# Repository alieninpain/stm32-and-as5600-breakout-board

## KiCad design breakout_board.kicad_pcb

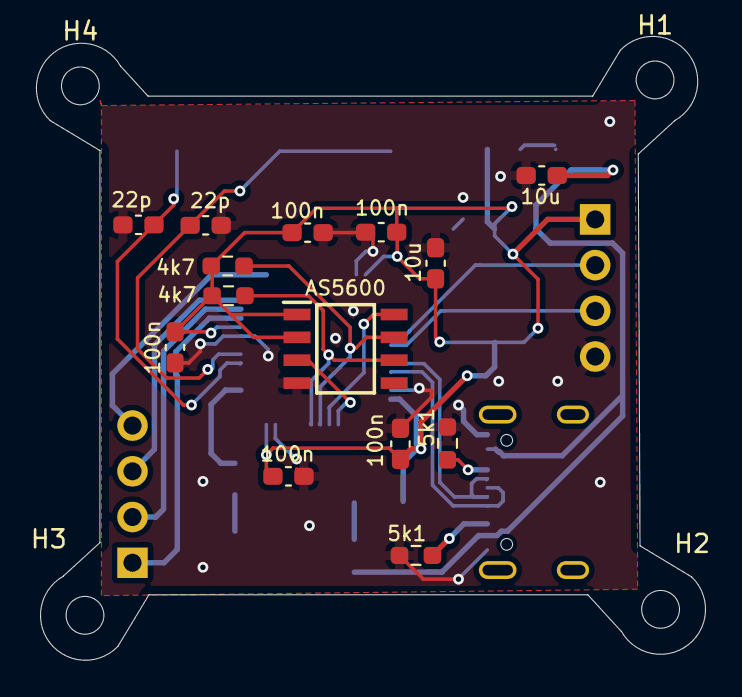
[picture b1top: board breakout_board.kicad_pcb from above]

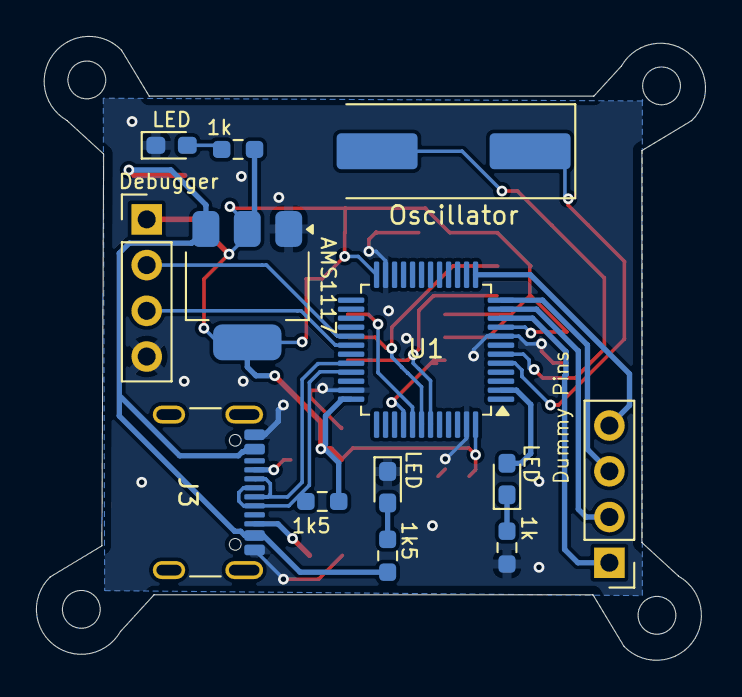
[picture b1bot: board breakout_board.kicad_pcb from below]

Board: 2 copper layers, 37.2 x 34.7 mm, 31 parts (13 on the bottom side), 23 nets.

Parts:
1k, 1k#2: 1k; R_0603_1608Metric_Pad0.98x0.95mm_HandSolder
1k5: 1k5; R_0603_1608Metric_Pad0.98x0.95mm_HandSolder
4k7: 4.7k; R_0603_1608Metric_Pad0.98x0.95mm_HandSolder
5k1: 5k1; R_0603_1608Metric_Pad0.98x0.95mm_HandSolder
10u: 10u; C_0603_1608Metric_Pad1.08x0.95mm_HandSolder
22p: 22p; C_0603_1608Metric_Pad1.08x0.95mm_HandSolder
100n: 100n; C_0603_1608Metric_Pad1.08x0.95mm_HandSolder
AMS1117: AMS1117-3.3; SOT-223-3_TabPin2
AS5600: AS5600-ASOT; SOIC127P600X175-8N
C6: 100n; C_0603_1608Metric_Pad1.08x0.95mm_HandSolder
C7: 22p; C_0603_1608Metric_Pad1.08x0.95mm_HandSolder
C9: 10u; C_0603_1608Metric_Pad1.08x0.95mm_HandSolder
D1, D2: LED; LED_0603_1608Metric_Pad1.05x0.95mm_HandSolder
DC, DC4: 100n; C_0603_1608Metric_Pad1.08x0.95mm_HandSolder
DC#2: 100n; C_0603_1608Metric_Pad1.08x0.95mm_HandSolder
H1, H2, H3, H4: MountingHole; MountingHole_2.1mm
J1: Dummy Pins; PinHeader_1x04_P2.54mm_Vertical
J2: Debugger; PinHeader_1x04_P2.54mm_Vertical
J3: USB_C_Receptacle_USB2.0_16P; USB_C_Receptacle_GCT_USB4105-xx-A_16P_TopMnt_Horizontal
LED: LED; LED_0603_1608Metric_Pad1.05x0.95mm_HandSolder
Oscillator: Crystal; Crystal_SMD_HC49-SD
R2: 4.7k; R_0603_1608Metric_Pad0.98x0.95mm_HandSolder
R4: 5k1; R_0603_1608Metric_Pad0.98x0.95mm_HandSolder
R7: 1k5; R_0603_1608Metric_Pad0.98x0.95mm_HandSolder
U1: STM32F103C8Tx; LQFP-48_7x7mm_P0.5mm

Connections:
DIR: AS5600.8 (DIR), U1.41 (PB5)
DP1: J1.1, U1.10 (PA0)
DP2: J1.2, U1.11 (PA1)
DP3: J1.3, U1.12 (PA2)
DP4: J1.4, U1.13 (PA3)
GND: 1k.1, 5k1.1, 10u.2, 22p.2, 100n.2, AMS1117.1 (GND), AS5600.4 (GND), C6.2, C7.2, C9.2, D2.1 (K), DC.2, DC4.2, DC#2.2, J2.4, J3.A1 (GND), J3.A12 (GND), J3.B1 (GND), J3.B12 (GND), LED.1 (K), R4.1, U1.8 (VSSA), U1.23 (VSS), U1.35 (VSS), U1.47 (VSS)
LED: D1.2 (A), U1.2 (PC13)
unnamed: 1k.2, D1.1 (K)
unnamed: D2.2 (A), R7.1
unnamed: 1k#2.1, LED.2 (A)
unnamed: 5k1.2, J3.A5 (CC1)
unnamed: J3.B5 (CC2), R4.2
OSC_IN: C7.1, Oscillator.1, U1.5 (PD0)
OSC_OUT: 22p.1, Oscillator.2, U1.6 (PD1)
OUT: AS5600.3 (OUT), U1.40 (PB4)
SCL_ENC: 4k7.2, AS5600.7 (SCL), U1.42 (PB6)
SDA_ENC: AS5600.6 (SDA), R2.1, U1.43 (PB7)
SWCLK: J2.3, U1.30 (PA9)
SWDIO: J2.2, U1.29 (PA8)
USB_D+: 1k5.1, J3.A6 (D+), J3.B6 (D+), U1.33 (PA12)
USB_D-: J3.A7 (D-), J3.B7 (D-), U1.32 (PA11)
VBUS: 10u.1, AMS1117.3 (VI), J3.A4 (VBUS), J3.A9 (VBUS), J3.B4 (VBUS), J3.B9 (VBUS), R7.2
VDD_c: 1k5.2, 1k#2.2, 4k7.1, 100n.1, AMS1117.2 (VO), AS5600.1 (VDD5V), AS5600.2 (VDD3V3), C6.1, C9.1, DC.1, DC4.1, DC#2.1, J2.1, R2.2, U1.9 (VDDA), U1.24 (VDD), U1.36 (VDD), U1.48 (VDD)

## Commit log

2026-02-17 add gerber and BOM files
2026-02-17 Bill of Materials file
2026-02-18 added return vias for ground
2026-02-18 added mounting holes
2026-02-18 Final BOM
2026-02-18 gerbers
2026-02-18 add gerber files
2026-02-19 upgraded
    silkscreen and minor fixes
2026-02-19 silkscreen +minor fixes
2026-02-19 final commit
2026-02-19 Cleaned repository
2026-02-20 Bunny ears
2026-02-20 updated gerber files
